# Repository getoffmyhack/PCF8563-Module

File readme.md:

PCF8563 Real Time Clock Module

[OSHPark Shared Project](https://oshpark.com/shared_projects/yfwEHxpi)

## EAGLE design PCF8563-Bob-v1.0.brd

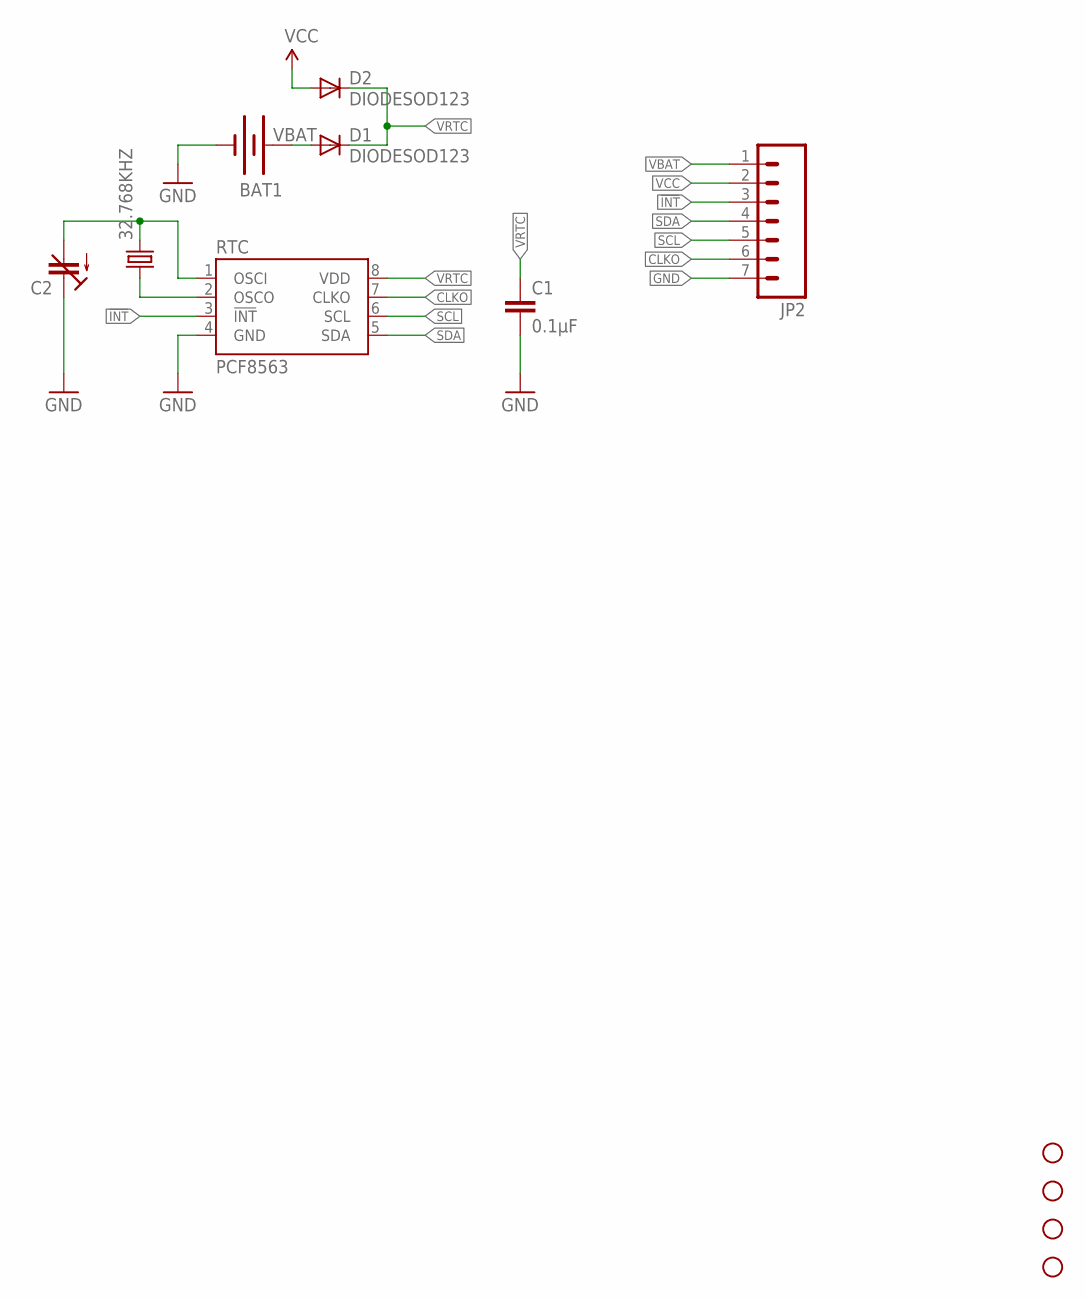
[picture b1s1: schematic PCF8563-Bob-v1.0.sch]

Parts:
32.768KHZ: CRYSTAL32-SMD; CRYSTAL-32KHZ-SMD
BAT1: BATTERY12SMD; HOLDER12SMD
C1: 0.1µF; 1206
C2: C-TRIMMTZC3; CTRIMTZC3
D1, D2: DIODESOD123; SOD123
JP2: M07; 1X07
RTC: PCF8563; DIL-08
STANDOFF1, STANDOFF2, STANDOFF3, STANDOFF4: STAND-OFF

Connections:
!INT: JP2.3, RTC.3 (!INT)
CLKO: JP2.6, RTC.7 (CLKO)
GND: BAT1.GND (-), C1.2, C2.2 (E), JP2.7, RTC.4 (GND)
unnamed: 32.768KHZ.X2 (2), C2.1 (A), RTC.1 (OSCI)
unnamed: 32.768KHZ.X1 (1), RTC.2 (OSCO)
SCL: JP2.5, RTC.6 (SCL)
SDA: JP2.4, RTC.5 (SDA)
VBAT: BAT1.PWR@1 (+), BAT1.PWR@2 (+), D1.1-A (A), JP2.1
VCC: D2.1-A (A), JP2.2
VRTC: C1.1, D1.2-C (C), D2.2-C (C), RTC.8 (VDD)

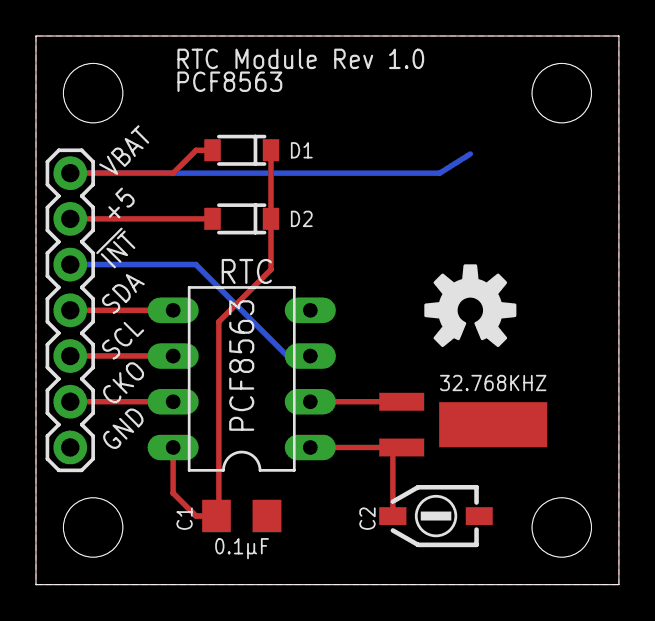
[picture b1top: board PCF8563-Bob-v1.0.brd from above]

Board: 2 copper layers, 32.4 x 30.5 mm, 13 parts (1 on the bottom side), 10 nets.

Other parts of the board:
U$2: OSHW-LOGO-M

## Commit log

2021-02-26 inital commit v1.0
2021-02-26 added readme
2021-02-26 update board image
2021-02-26 added assembled pic. fixed readme
2021-02-26 added OSHPark renditions; updated readme
2021-02-26 added schematic PDF; updated readme

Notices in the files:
parts and their libraries:
SparkFun-Capacitors: Licensing: Creative Commons ShareAlike 4.0 International - https://creativecommons.org/licenses/by-sa/4.0
SparkFunOld: Licensing: CC v3.0 Share-Alike You are welcome to use this library for commercial purposes.
